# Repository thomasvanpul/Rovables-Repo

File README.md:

# Rovables, forked

This is a fork of [adementyev/Rovables-Repo](https://github.com/adementyev/Rovables-Repo), the design files for
Rovables, the miniature on-body robots by Artem Dementyev, Hsin-Liu (Cindy) Kao, Inrak Choi, Deborah Ajilo,
Maggie Xu, Sean Follmer, Joe Paradiso and Chris Schmandt, with the undergraduate students they name below
(MIT Media Lab and Stanford Shape Lab, UIST 2016).
Their work is MIT licensed (`LICENSE.md`) and is kept here unchanged. Their README follows below, as they wrote it.

## What this fork adds

Everything the original authors made is where they left it. Additions are in new folders only:

| Folder | What | State |
|---|---|---|
| `mechanical/converted/` | Their SolidWorks parts as STEP and STL, so they open without SolidWorks | 11 of 11 custom parts converted |
| `printables/` | The parts oriented and plated for an FDM printer (Bambu P1S, PLA), with the script that builds them | sliced, not yet printed |
| `electronics/kicad/` | Their six Altium boards imported into KiCad 10 | boards import and open; four schematics converted, 139 of 141 nets identical to the boards |
| `electronics/bom/` | One parts list with stock and price per line, and what two sets cost | checked 16 Nov 2026 |

A redesign, Rovable v2 (N20 motors, rod magnets as the wheels, one ESP32 over Bluetooth in place of the separate
radio and base station), is on the [`v2` branch](https://github.com/thomasvanpul/Rovables-Repo/tree/v2). It is
kept off this branch so that everything here stays the original design and conversions of it. On 16 Nov 2026 it
is modelled and sliced and its firmware compiles; it has not been printed or driven.

Fork maintained by Thomas van Pul. Additions are under the same MIT licence.

---

# Rovables Project 

## Introduction
This repository has all the design files to assemble the robots. Rovables are miniature wearable robots that can move around the body. 
See the paper we published at UIST conference [here](http://www.artemdementyev.com/wp-content/uploads/2016/10/Rovables-Miniature-On-Body-Robots-as-Mobile-Wearables.pdf).  

## Content
electronics/ - contains the circuit boards design. They were all designed using Altium, so it might be required to see the original files

mechanical/ - This folder contains mechanical files, done in SolidWorks 2016. 

software/ - contains the software that runs on the devices. We used the Arduino platform, so the robots can be easily programmed.  

## Manufacturing and design
The design contains many 3D printed custom parts and custom circuit boards. Making the design will require at least a good resolution 3D printer (Formlabs or Eden260). Other printers might work also, but we haven't tried them. 

## Known Issues
The same nRF42 library is used for the robot and the receiver. Change in nRF52.cpp file: #define TEENSY_MASTER_BOARD depending on which one, since they use different SPI port definitions. 

The localization of the robot is not implemented in the current code. This version has high resolution wheel encoders and a powerful ARM processor, so the tracking will be better. 

## Aknowledgements
This project was a collaboration between MIT Media Lab (Responsive Environments and Living Mobile) and Shape Lab at Stanford University

The poeple who worked on this project are:

Graduate students: Artem Dementyev, Hsin-Liu (Cindy) Kao, Inrak Choi, Deborah Ajilo, Maggie Xu. 

The faculty: Sean Follmer, Joe Paradiso, Chris Schmandt.

Undegraduate students: Lucas Santana, Karla-Sofia Zapata-Garcia, Cheyenne Hua, and Diana Lamaute

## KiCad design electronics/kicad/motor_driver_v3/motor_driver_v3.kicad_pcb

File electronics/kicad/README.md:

# KiCad imports (added in this fork)

The six Altium boards, imported into KiCad so they open without Altium. One folder per board, each with the
`.kicad_pcb`, a top-side render, the importer's report and a statistics file.

Made with `kicad-cli pcb import --format altium` from KiCad 10.0.3, so the files are in KiCad 10 format and
need KiCad 10 or newer. Every board imported with return code 0 and no importer errors, then loaded again
for a design-rule check and a 3D render.

| Board | Source | Copper layers | Thickness mm | Size mm | Footprints | Min track / gap mm | Smallest via drill mm |
|---|---|---|---|---|---|---|---|
| `motor_driver_v3` (the robot's main board) | `Motor driver v3/PCB_motor_driver_v3.PcbDoc` | 4 | 0.57 | 23.2 x 22.2 | 69 | 0.127 / 0.127 | 0.2 |
| `ir_encoder_v2` | `IR encoder/PCB_IR_Encoder_v2.PcbDoc` | 2 | 0.41 | 10.1 x 6.4 | 7 | 0.254 / 0.127 | 0.2 |
| `encoder_flex_cable` | `IR encoder/PCB_Flex_cable_Encoder.PcbDoc` | 2 | 0.14 | 9.1 x 8.7 | 8 | n/a | none |
| `encoder_wheel` | `Encoder wheel/PCB_Encoder_v2_single_16.PcbDoc` | 2 | 0.41 | 9.4 x 9.4 | 3 | n/a | 1.0 |
| `master_board` (USB base station) | `master board/PCB_rovables_master_v1.PcbDoc` | 2 | 1.49 | 45.3 x 39.4 | 17 | 0.406 / 0.254 | 0.9 |
| `programming_shield` | `Programming adapter/PCB_Shield_for_Rovables_v2.PcbDoc` | 2 | 0.41 | 18.2 x 36.1 | 6 | 0.152 / 0.152 | 0.2 |

Known gaps:

- `motor_driver_v3` and `encoder_flex_cable` imported with degenerate sub-micron segments and micro-gaps on Edge.Cuts; those were cleaned and snapped into closed outlines so both boards report `has_outline: true` and plot cleanly.
- The design-rule check reports violations on every board (motor driver 1144, shield 553, master 146, encoder 60, flex 56, wheel 42). They are almost all KiCad's default rules being stricter than the 0.127 mm tracks and 0.2 mm vias these boards were drawn with; no board has unconnected nets.
- The importer skipped Altium's unused internal plane layers on every board.

## Schematics

The four Altium schematics are converted too: `<board>/<board>.kicad_sch`, with a PDF and a PNG of the sheet
beside each. KiCad 10.0.3 imports an Altium schematic only from the schematic editor's window (File, Import,
Non-KiCad Schematic) and `kicad-cli` has no schematic import, so `altium_sch_import.py` in this folder reads the
`.SchDoc` records directly and writes the KiCad file. Each placed component becomes its own symbol drawn from
the Altium graphics, with the wires, junctions, net labels and power ports carried over. Rebuild and re-check
with `python3 electronics/kicad/altium_sch_import.py --check`.

The check loads each schematic with `kicad-cli`, exports its netlist and compares it pin by pin with the nets
on the imported board (`sch_check.json` in each folder; net names are ignored, a net is the set of pins on it).

| Schematic | Components | Loads in kicad-cli | Pins compared with the board | Nets identical |
|---|---|---|---|---|
| `motor_driver_v3` | 58 | yes | 241 | 75 of 76 |
| `ir_encoder_v2` | 6 | yes | 17 | 6 of 6 |
| `programming_shield` | 6 | yes | 61 | 24 of 25 |
| `master_board` | 14 | yes | 100 | 34 of 34 |

The two nets that differ are differences between the authors' own schematic and board, not conversion faults:

- Motor driver, VBAT: the schematic joins C23.1, U4.3, connector P4 pin 1 and the on/off switch SW1. On the
  board the switch footprint is named `*1`, and P4 pin 1 is not on VBAT.
- Programming shield, RESET: the schematic puts P4 pin 1 on RESET with P1.10, P5.10 and P6.4; the board does not.

Limits of the conversion: there is no flex-cable or encoder-wheel schematic in the authors' files, so those
two boards have none. Footprint names are the Altium ones and are not linked to the KiCad footprints on the
boards. The electrical rules check reports unconnected pins and undriven power pins the Altium sheets also
have (counts in each `sch_check.json`), plus library warnings because the symbols live inside the schematic.
The embedded logo image and the title-block field values are not carried over. The authors' schematic PDFs
still sit next to each `.SchDoc`.

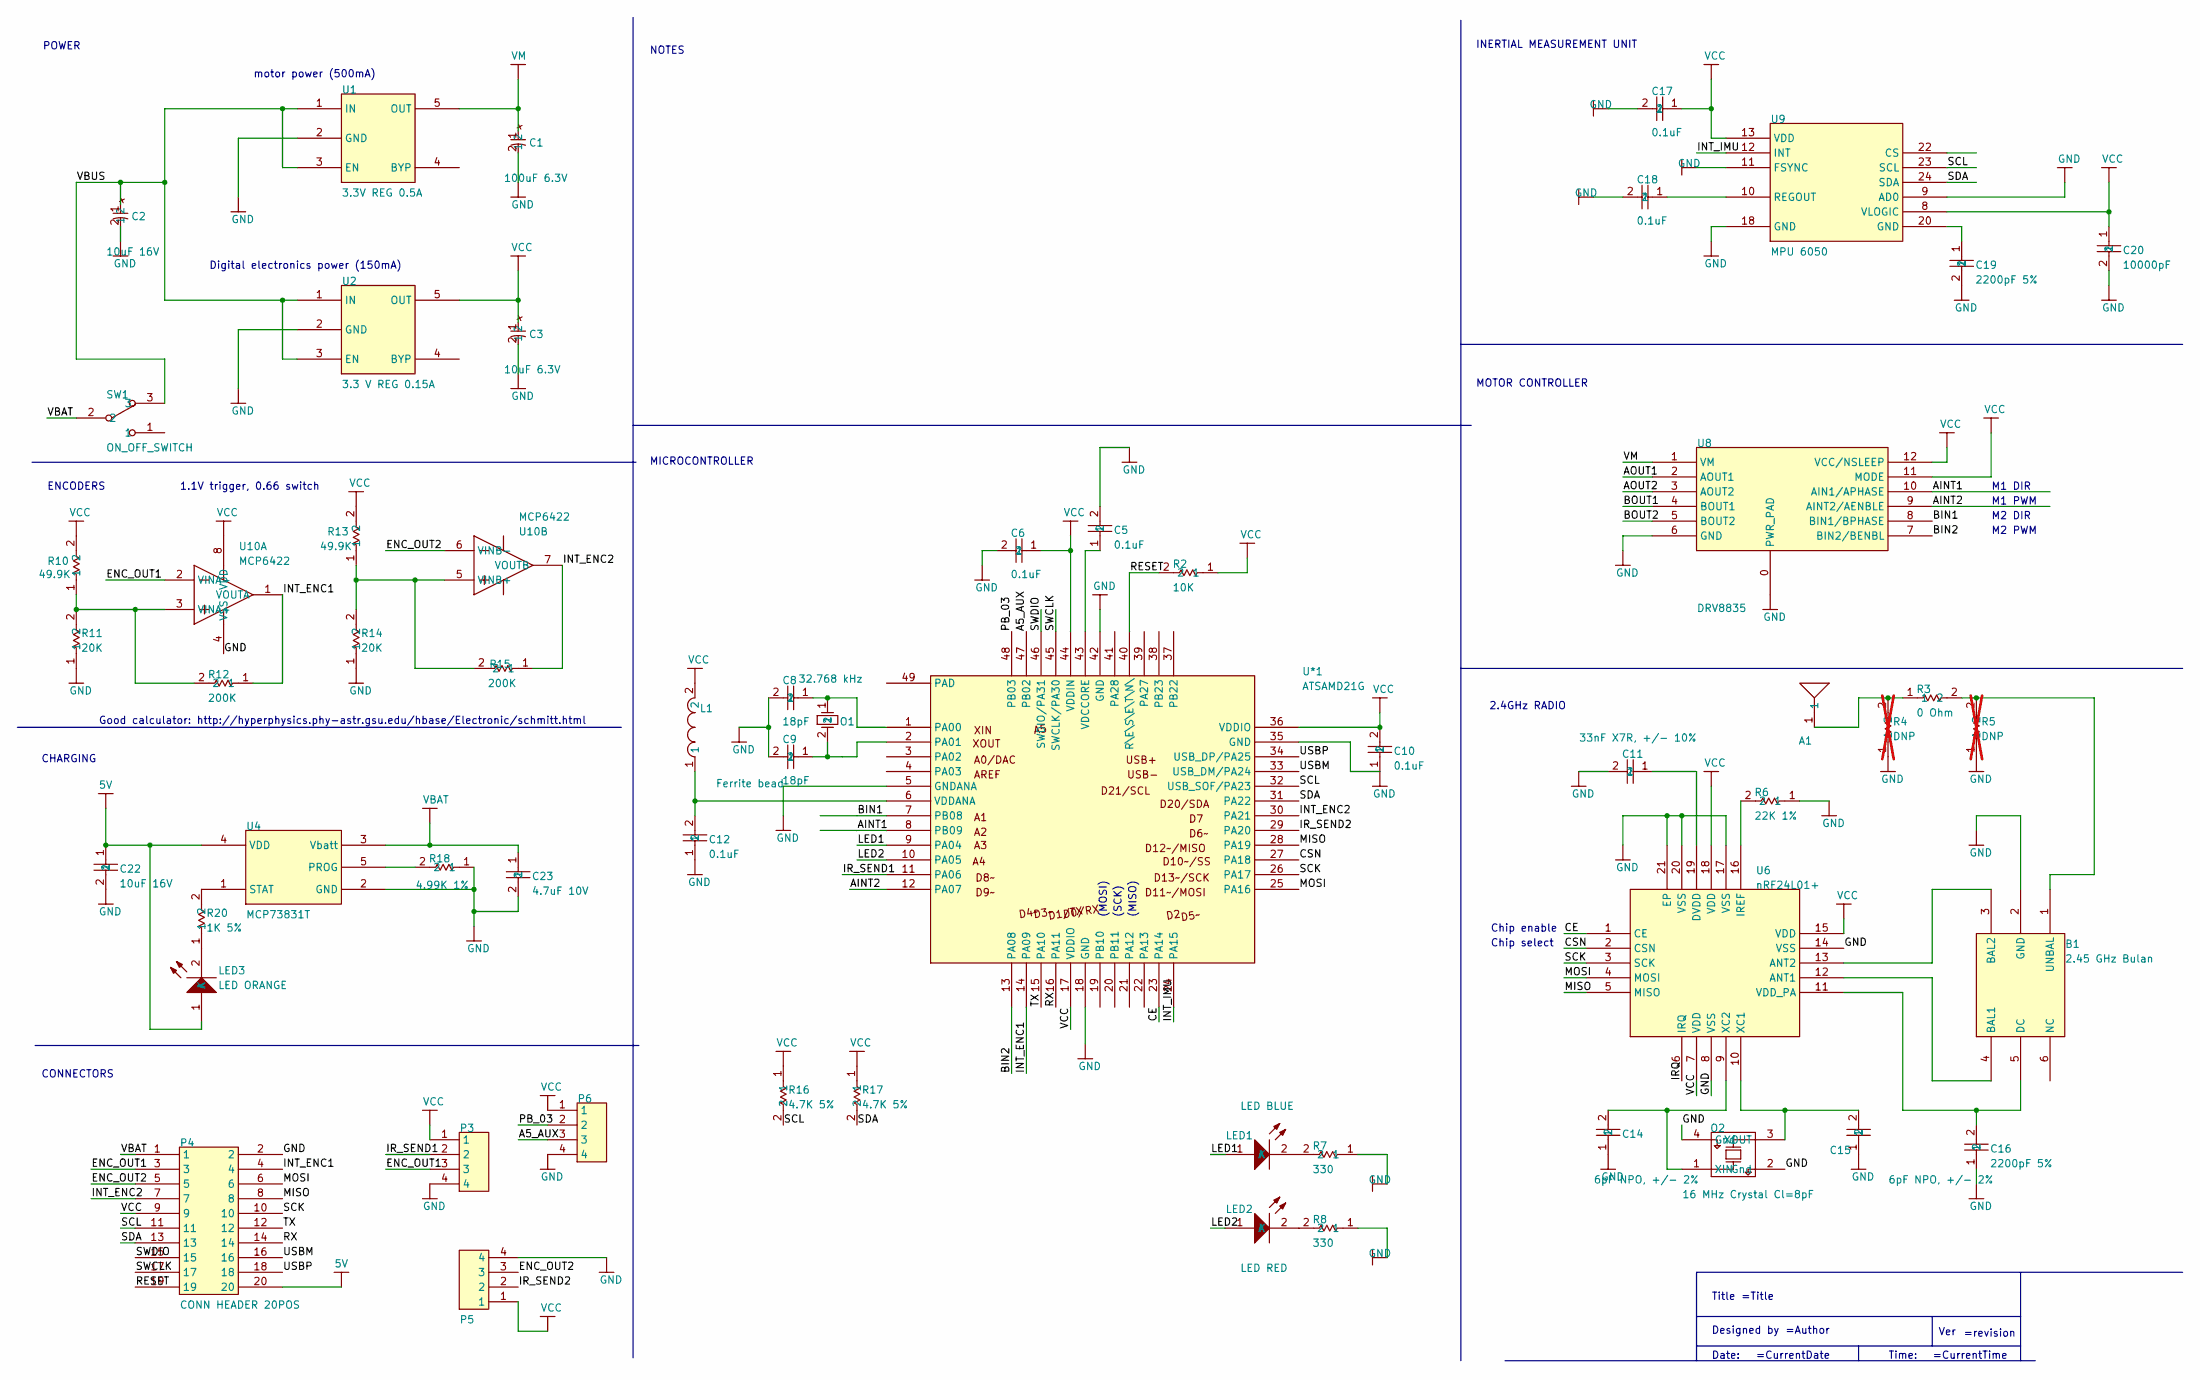
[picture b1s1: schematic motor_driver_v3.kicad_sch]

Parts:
A1: 2.4GHz SMT On-ground MID Chip Antenna; 47948-0001
B1: 2.45 GHz Bulan; 2450BM14A0002
C1: 100uF 6.3V; CAP1206
C2: 10uF 16V; CAP0805
C3: 10uF 6.3V; 0805 TANTALUM
C5, C12: 0.1uF; 0603W
C6, C10, C17, C18: 0.1uF; 0402 CAPACITOR
C8, C9: 18pF; 0402 CAPACITOR
C11: 33nF X7R, +/- 10%; 0402 CAPACITOR
C14, C15: 6pF NPO, +/- 2%; 0402 CAPACITOR
C16, C19: 2200pF 5%; 0402 CAPACITOR
C20: 10000pF; 0402 CAPACITOR
C22: 10uF 16V; 0603W
C23: 4.7uF 10V; 0603W
L1: Ferrite bead; 0603W
LED1: LED BLUE; 0402W
LED2: LED RED; 0402W
LED3: LED ORANGE; 0402W
O1: 32.768 kHz; 32.768 Crystal
O2: 16 MHz Crystal Cl=8pF; 2.5 x 2.0 crystal
P3, P5, P6: FH33J-4S-0.5SH(99)
P4: CONN HEADER 20POS; DF12 20 POS
R2: 10K; 0402 RESISTOR
R3: 0 Ohm; 0402 RESISTOR
R4, R5: DNP; 0402 RESISTOR; not fitted
R6: 22K 1%; 0402 RESISTOR
R7, R8: 330; 0402 RESISTOR
R10, R13: 49.9K; 0603W
R11, R14: 20K; 0603W
R12, R15: 200K; 0603W
R16, R17: 4.7K 5%; 0402 RESISTOR
R18: 4.99K 1%; 0603W
R20: 1K 5%; 0603W
SW1: ON_OFF_SWITCH; SWTICH_SMD_SIDE
U1: 3.3V REG 0.5A; SOT-23-5
U2: 3.3 V REG 0.15A; SOT-23-5
U4: MCP73831T; SOT-23-5
U6: nRF24L01+; QFN20
U8: DRV8835; WSON-16
U9: MPU 6050; QFN24
U10: MCP6422; MSOP-MS8_N
U*1: ATSAMD21G; TQFN48

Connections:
5V: C22.1, LED3.1 (A), P4.20, U4.4 (VDD)
A5_AUX: P6.3, U*1.47 (PB02)
AINT1: U8.10 (AIN1/APHASE), U*1.8 (PB09)
AINT2: U8.9 (AINT2/AENBLE), U*1.12 (PA07)
AOUT1: U8.2 (AOUT1)
AOUT2: U8.3 (AOUT2)
BIN1: U8.8 (BIN1/BPHASE), U*1.7 (PB08)
BIN2: U8.7 (BIN2/BENBL), U*1.13 (PA08)
BOUT1: U8.4 (BOUT1)
BOUT2: U8.5 (BOUT2)
CE: U6.1 (CE), U*1.23 (PA14)
CSN: U6.2 (CSN), U*1.27 (PA18)
ENC_OUT1: P3.3, P4.3, U10.2 (VINA-)
ENC_OUT2: P4.5, P5.3, U10.6 (VINB-)
GND: B1.2 (GND), C1.2, C2.2, C3.2, C5.2, C6.2, C8.2, C9.2, C10.1, C11.2, C12.1, C14.1, C15.1, C16.1, C17.2, C18.2, C19.2, C20.2, C22.2, C23.2, O2.2 (Gnd), O2.4 (Gnd), P3.4, P4.2, P5.4, P6.4, R4.1, R5.1, R6.1, R7.1, R8.1, R11.1, R14.1, R18.1, U1.2 (GND), U2.2 (GND), U4.2 (GND), U6.8 (VSS), U6.14 (VSS), U6.17 (VSS), U6.20 (VSS), U6.21 (EP), U8.0 (PWR_PAD), U8.6 (GND), U9.9 (AD0), U9.11 (FSYNC), U9.18 (GND), U10.4 (VSS), U*1.5 (GNDANA), U*1.18 (GND), U*1.35 (GND), U*1.42 (GND)
INT_ENC1: P4.4, R12.1, U10.1 (VOUTA), U*1.14 (PA09)
INT_ENC2: P4.7, R15.1, U10.7 (VOUTB), U*1.30 (PA21)
INT_IMU: U9.12 (INT), U*1.24 (PA15)
IRQ: U6.6 (IRQ)
IR_SEND1: P3.2, U*1.11 (PA06)
IR_SEND2: P5.2, U*1.29 (PA20)
LED1: LED1.1 (A), U*1.9 (PA04)
LED2: LED2.1 (A), U*1.10 (PA05)
MISO: P4.8, U6.5 (MISO), U*1.28 (PA19)
MOSI: P4.6, U6.4 (MOSI), U*1.25 (PA16)
NetA1_1: A1.1, R3.1, R4.2
NetB1_1: B1.1 (UNBAL), R3.2, R5.2
NetB1_3: B1.3 (BAL2), U6.13 (ANT2)
NetB1_4: B1.4 (BAL1), U6.12 (ANT1)
NetB1_5: B1.5 (DC), C16.2, U6.11 (VDD_PA)
NetC5_1: C5.1, U*1.43 (VDCCORE)
NetC8_1: C8.1, O1.1, U*1.1 (PA00)
NetC9_1: C9.1, O1.2, U*1.2 (PA01)
NetC11_1: C11.1, U6.19 (DVDD)
NetC12_2: C12.2, L1.1, U*1.6 (VDDANA)
NetC14_2: C14.2, O2.1 (XIN), U6.9 (XC2)
NetC15_2: C15.2, O2.3 (XOUT), U6.10 (XC1)
NetC18_1: C18.1, U9.10 (REGOUT)
NetC19_1: C19.1, U9.20 (GND)
NetLED1_2: LED1.2 (K), R7.2
NetLED2_2: LED2.2 (K), R8.2
NetLED3_2: LED3.2 (K), R20.1
NetR6_2: R6.2, U6.16 (IREF)
NetR10_1: R10.1, R11.2, R12.2, U10.3 (VINA+)
NetR13_1: R13.1, R14.2, R15.2, U10.5 (VINB+)
NetR18_2: R18.2, U4.5 (PROG)
NetR20_2: R20.2, U4.1 (STAT)
PB_03: P6.2, U*1.48 (PB03)
RESET: P4.19, R2.2, U*1.40 (R\E\S\E\T\N\)
RX: P4.14, U*1.16 (PA11)
SCK: P4.10, U6.3 (SCK), U*1.26 (PA17)
SCL: P4.11, R16.2, U9.23 (SCL), U*1.32 (USB_SOF/PA23)
SDA: P4.13, R17.2, U9.24 (SDA), U*1.31 (PA22)
SWCLK: P4.17, U*1.45 (SWCLK/PA30)
SWDIO: P4.15, U*1.46 (SWDIO/PA31)
TX: P4.12, U*1.15 (PA10)
USBM: P4.16, U*1.33 (USB_DM/PA24)
USBP: P4.18, U*1.34 (USB_DP/PA25)
VBAT: C23.1, P4.1, SW1.2, U4.3 (Vbatt); also elsewhere on the board
VBUS: C2.1, SW1.3, U1.1 (IN), U1.3 (EN), U2.1 (IN), U2.3 (EN); also elsewhere on the board
VCC: C3.1, C6.1, C10.2, C17.1, C20.1, L1.2, P3.1, P4.9, P5.1, P6.1, R2.1, R10.2, R13.2, R16.1, R17.1, U2.5 (OUT), U6.7 (VDD), U6.15 (VDD), U6.18 (VDD), U8.11 (MODE), U8.12 (VCC/NSLEEP), U9.8 (VLOGIC), U9.13 (VDD), U10.8 (VDD), U*1.17 (VDDIO), U*1.36 (VDDIO), U*1.44 (VDDIN)
VM: C1.1, U1.5 (OUT), U8.1 (VM)

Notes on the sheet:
=revision
=CurrentDate
=CurrentTime
Title
Date:
Time:
Designed by
=Title
=Author
Ver
M2 PWM
M2 DIR
M1 PWM
M1 DIR
Chip enable
Chip select
2.4GHz RADIO
MOTOR CONTROLLER
INERTIAL MEASUREMENT UNIT
MICROCONTROLLER
CONNECTORS
ENCODERS
POWER
CHARGING
NOTES
motor power (500mA)
1.1V trigger, 0.66 switch
(MISO)
(MOSI)
(SCK)
Good calculator: http://hyperphysics.phy-astr.gsu.edu/hbase/Electronic/schmitt.html
Digital electronics power (150mA)

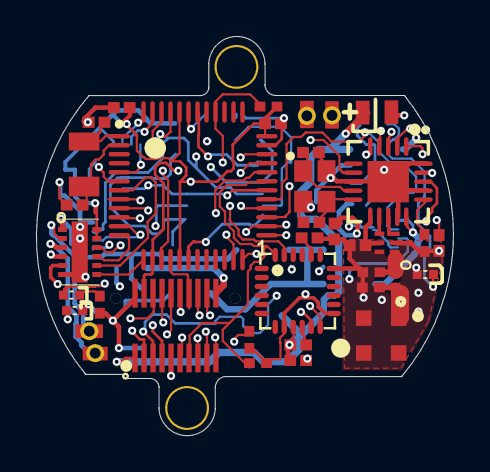
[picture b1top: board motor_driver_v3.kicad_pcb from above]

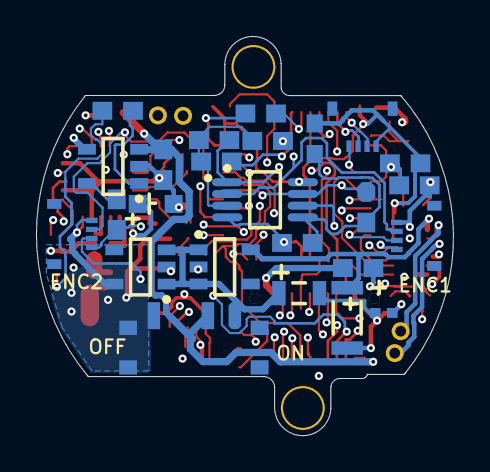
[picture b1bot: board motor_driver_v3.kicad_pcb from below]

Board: 4 copper layers, 23.2 x 22.2 mm, 57 parts (25 on the bottom side), 57 nets.

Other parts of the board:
*1: ON_OFF_SWITCH; SWTICH_SMD_SIDE

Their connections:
VBAT: *1.2; also elsewhere on the board
VBUS: *1.3; also elsewhere on the board

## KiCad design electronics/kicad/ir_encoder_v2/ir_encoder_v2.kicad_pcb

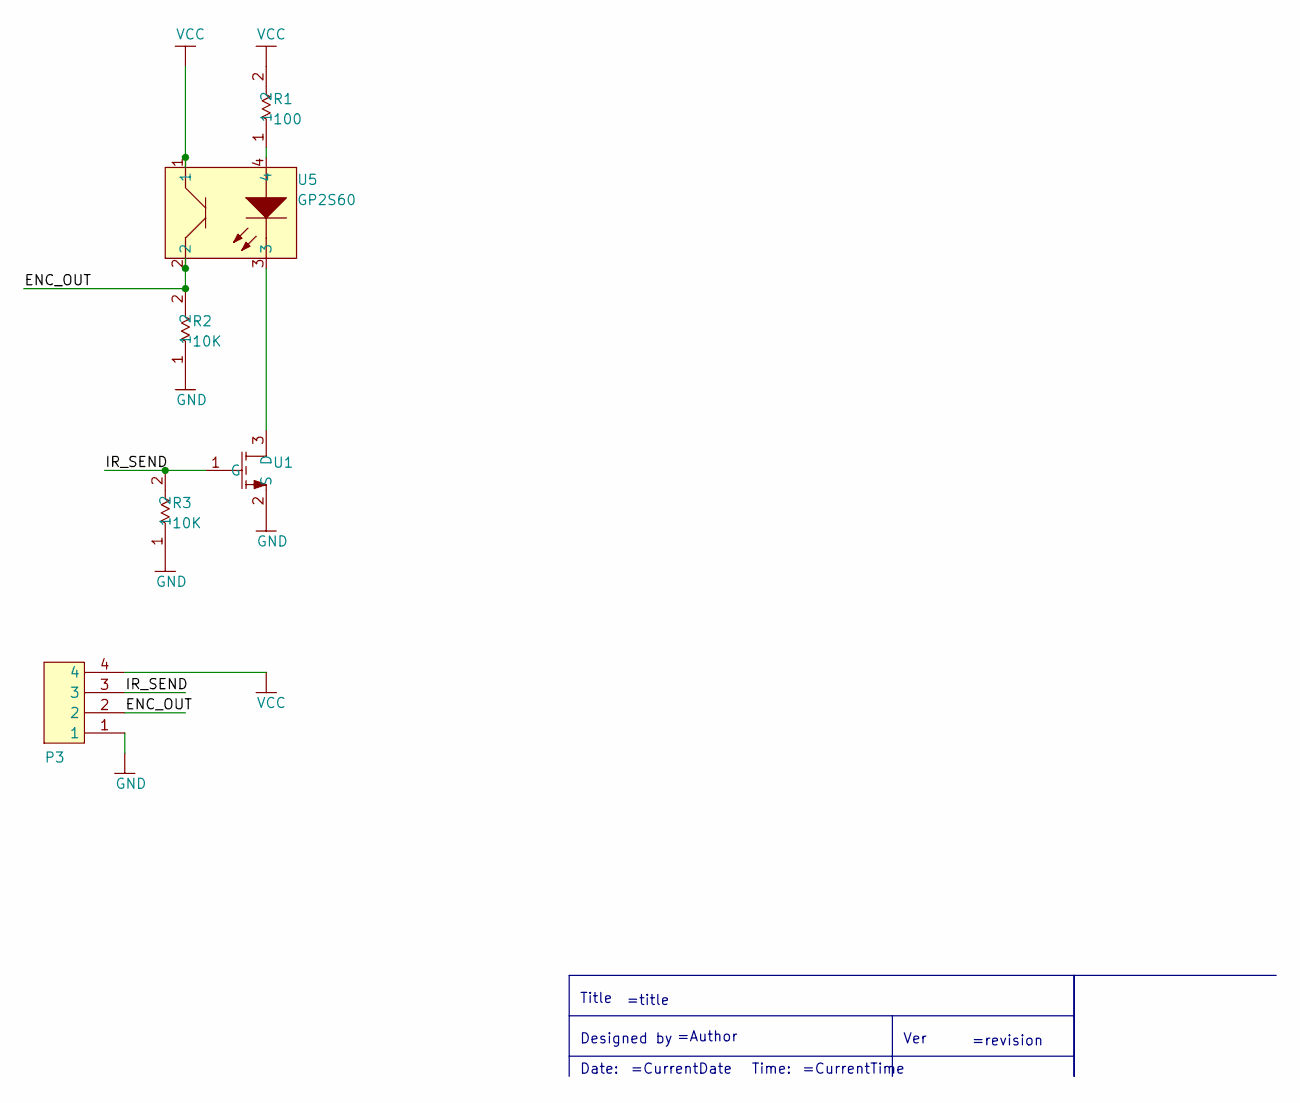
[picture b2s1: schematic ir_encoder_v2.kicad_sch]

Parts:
P3: FH33J-4S-0.5SH(99)
R1: 100; 0603W
R2, R3: 10K; 0603W
U1: MOSFET N CHANNEL; SOT323
U5: GP2S60

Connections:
ENC_OUT: P3.2, R2.2, U5.2
GND: P3.1, R2.1, R3.1, U1.2 (S)
IR_SEND: P3.3, R3.2, U1.1 (G)
NetR1_1: R1.1, U5.4
NetU1_3: U1.3 (D), U5.3
VCC: P3.4, R1.2, U5.1

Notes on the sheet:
=title
=revision
=CurrentDate
=CurrentTime
Title
Date:
Ver
Time:
Designed by
=Author

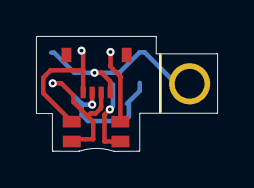
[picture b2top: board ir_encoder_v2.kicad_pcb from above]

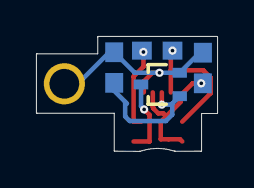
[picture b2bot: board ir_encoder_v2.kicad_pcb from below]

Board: 2 copper layers, 10.1 x 6.4 mm, 6 parts (4 on the bottom side), 6 nets.

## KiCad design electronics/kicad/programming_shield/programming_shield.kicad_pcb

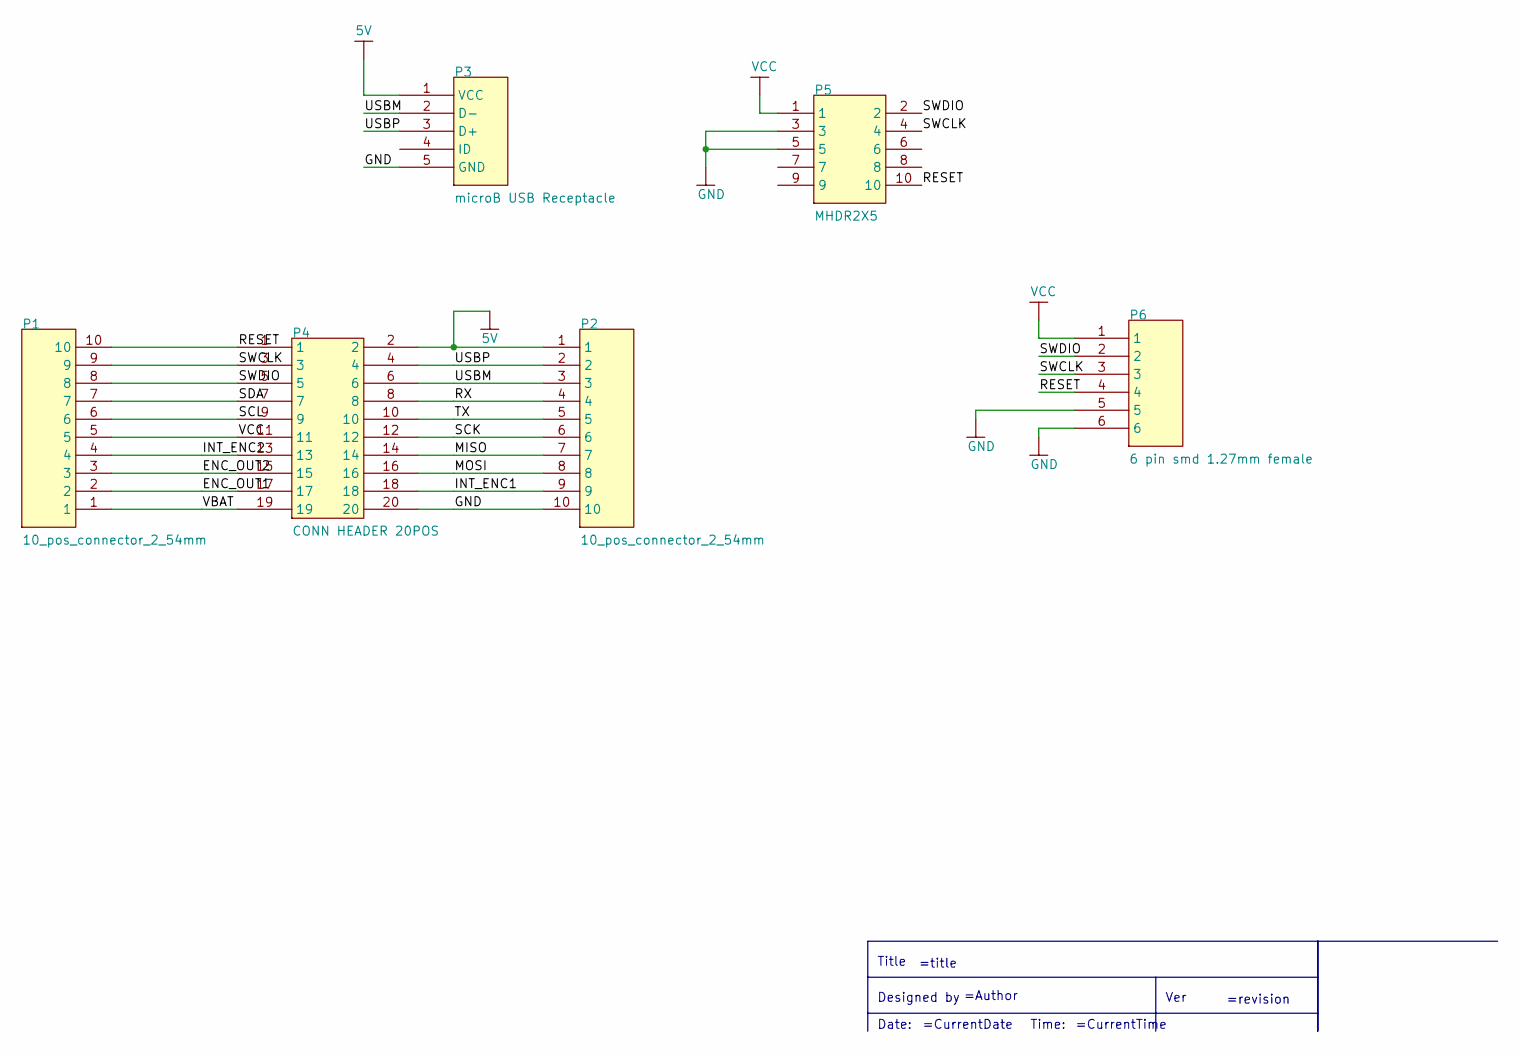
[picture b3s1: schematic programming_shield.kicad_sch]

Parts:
P1, P2: 10_pos_connector_2_54mm; 2_54mm_10_pos_connector
P3: microB USB Receptacle; MicroB USB Standarad SMT
P4: CONN HEADER 20POS; DF12 20 POS
P5: MHDR2X5
P6: 6 pin smd 1.27mm female; 6pos 1.27mm

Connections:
5V: P2.1, P3.1 (VCC), P4.2
ENC_OUT1: P1.2, P4.17
ENC_OUT2: P1.3, P4.15
GND: P2.10, P3.5 (GND), P4.20, P5.3, P5.5, P6.5, P6.6
INT_ENC1: P2.9, P4.18
INT_ENC2: P1.4, P4.13
MISO: P2.7, P4.14
MOSI: P2.8, P4.16
RESET: P1.10, P4.1, P5.10, P6.4
RX: P2.4, P4.8
SCK: P2.6, P4.12
SCL: P1.6, P4.9
SDA: P1.7, P4.7
SWCLK: P1.9, P4.3, P5.4, P6.3
SWDIO: P1.8, P4.5, P5.2, P6.2
TX: P2.5, P4.10
USBM: P2.3, P3.2 (D-), P4.6
USBP: P2.2, P3.3 (D+), P4.4
VBAT: P1.1, P4.19
VCC: P1.5, P4.11, P5.1, P6.1

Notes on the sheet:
=title
=revision
=CurrentDate
=CurrentTime
Title
Date:
Ver
Time:
Designed by
=Author

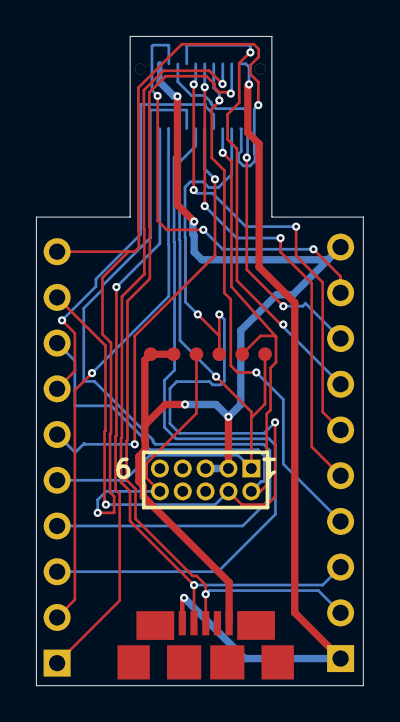
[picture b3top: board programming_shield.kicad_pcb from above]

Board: 2 copper layers, 18.2 x 36.1 mm, 6 parts (1 on the bottom side), 20 nets.

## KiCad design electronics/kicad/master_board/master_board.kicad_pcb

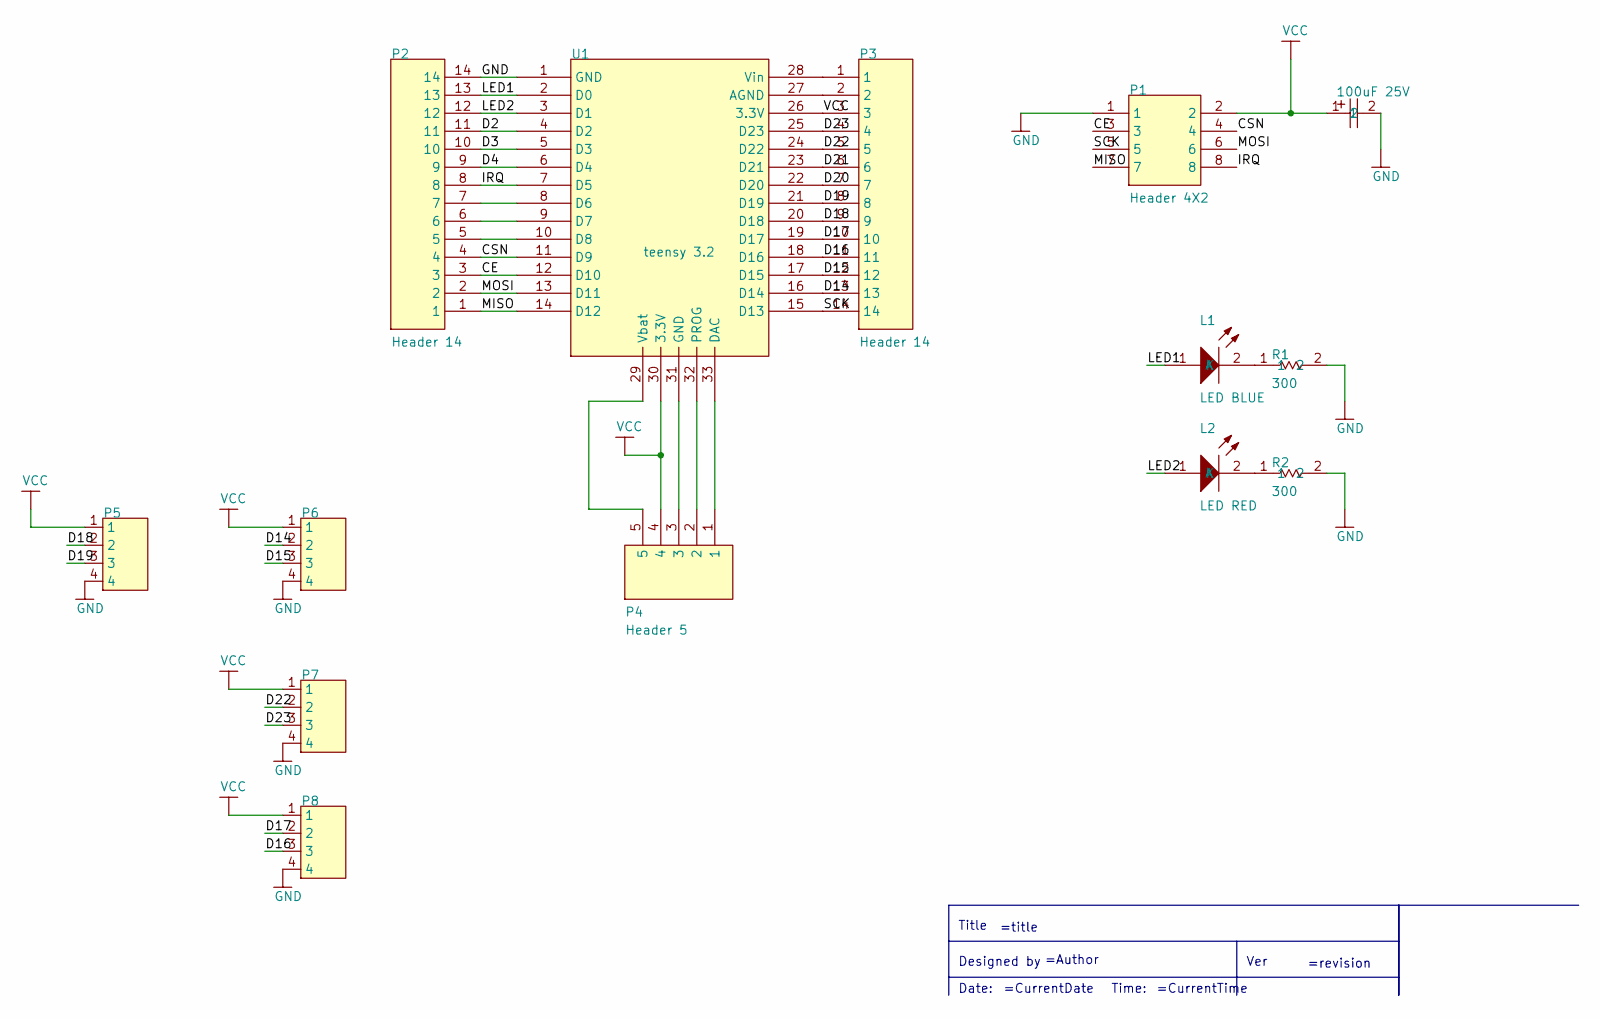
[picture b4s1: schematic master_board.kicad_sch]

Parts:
100uF 25V: Electrolytic Cap 100uF smd; F80 Electrolytic cap
L1: LED BLUE; RES_1206_SMD
L2: LED RED; RES_1206_SMD
P1: Header 4X2; HDR2X4
P2, P3: Header 14; HDR1X14
P4: Header 5; HDR1X5
P5, P6, P7, P8: JST SH 4 SIDE; JST SH 4 TOP ENTRY
R1, R2: 300; RES_1206_SMD
U1: teensy 3.2; Teensy 3.2

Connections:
CE: P1.3, P2.3, U1.12 (D10)
CSN: P1.4, P2.4, U1.11 (D9)
D2: P2.11, U1.4 (D2)
D3: P2.10, U1.5 (D3)
D4: P2.9, U1.6 (D4)
D14: P3.13, P6.2, U1.16 (D14)
D15: P3.12, P6.3, U1.17 (D15)
D16: P3.11, P8.3, U1.18 (D16)
D17: P3.10, P8.2, U1.19 (D17)
D18: P3.9, P5.2, U1.20 (D18)
D19: P3.8, P5.3, U1.21 (D19)
D20: P3.7, U1.22 (D20)
D21: P3.6, U1.23 (D21)
D22: P3.5, P7.2, U1.24 (D22)
D23: P3.4, P7.3, U1.25 (D23)
GND: 100uF 25V.2, P1.1, P2.14, P5.4, P6.4, P7.4, P8.4, R1.2, R2.2, U1.1 (GND)
IRQ: P1.8, P2.8, U1.7 (D5)
LED1: L1.1 (A), P2.13, U1.2 (D0)
LED2: L2.1 (A), P2.12, U1.3 (D1)
MISO: P1.7, P2.1, U1.14 (D12)
MOSI: P1.6, P2.2, U1.13 (D11)
NetL1_2: L1.2 (K), R1.1
NetL2_2: L2.2 (K), R2.1
NetP2_5: P2.5, U1.10 (D8)
NetP2_6: P2.6, U1.9 (D7)
NetP2_7: P2.7, U1.8 (D6)
NetP3_1: P3.1, U1.28 (Vin)
NetP3_2: P3.2, U1.27 (AGND)
NetP4_1: P4.1, U1.33 (DAC)
NetP4_2: P4.2, U1.32 (PROG)
NetP4_3: P4.3, U1.31 (GND)
NetP4_5: P4.5, U1.29 (Vbat)
SCK: P1.5, P3.14, U1.15 (D13)
VCC: 100uF 25V.1, P1.2, P3.3, P4.4, P5.1, P6.1, P7.1, P8.1, U1.26 (3.3V), U1.30 (3.3V)

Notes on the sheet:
=title
=revision
=CurrentDate
=CurrentTime
Title
Date:
Ver
Time:
Designed by
=Author

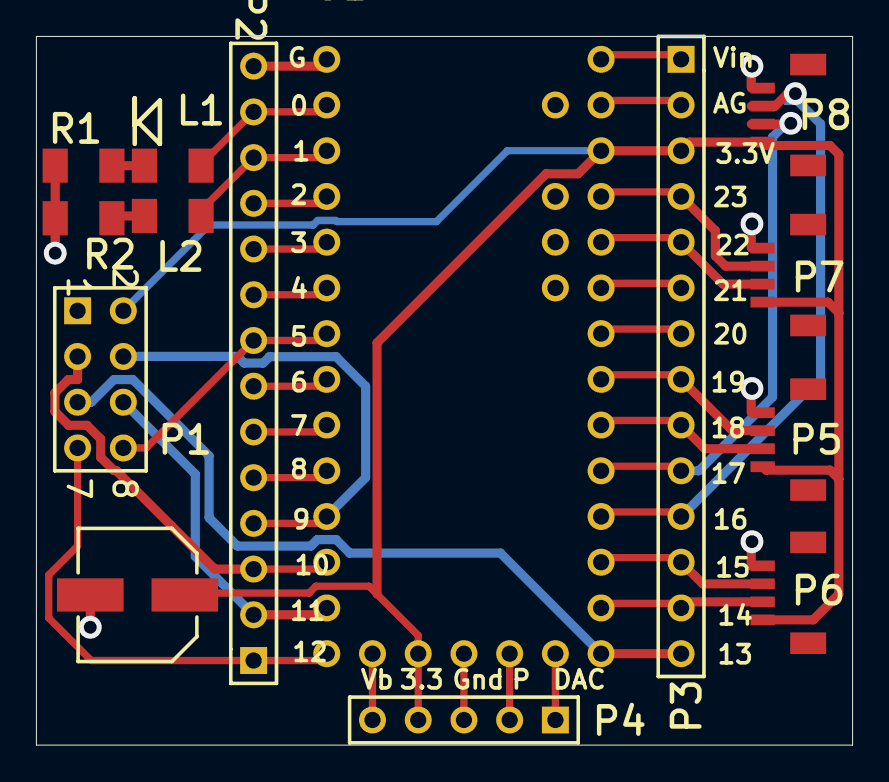
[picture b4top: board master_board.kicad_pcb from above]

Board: 2 copper layers, 45.3 x 39.4 mm, 14 parts (0 on the bottom side), 34 nets.
